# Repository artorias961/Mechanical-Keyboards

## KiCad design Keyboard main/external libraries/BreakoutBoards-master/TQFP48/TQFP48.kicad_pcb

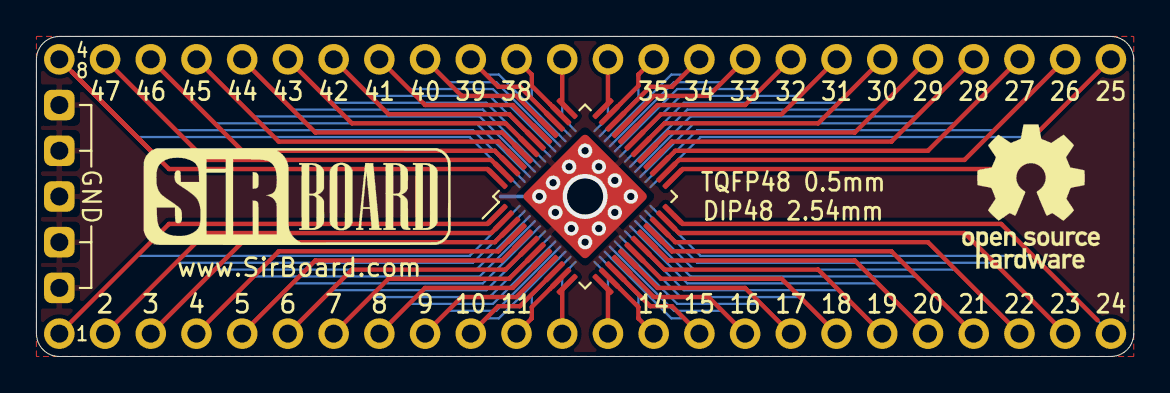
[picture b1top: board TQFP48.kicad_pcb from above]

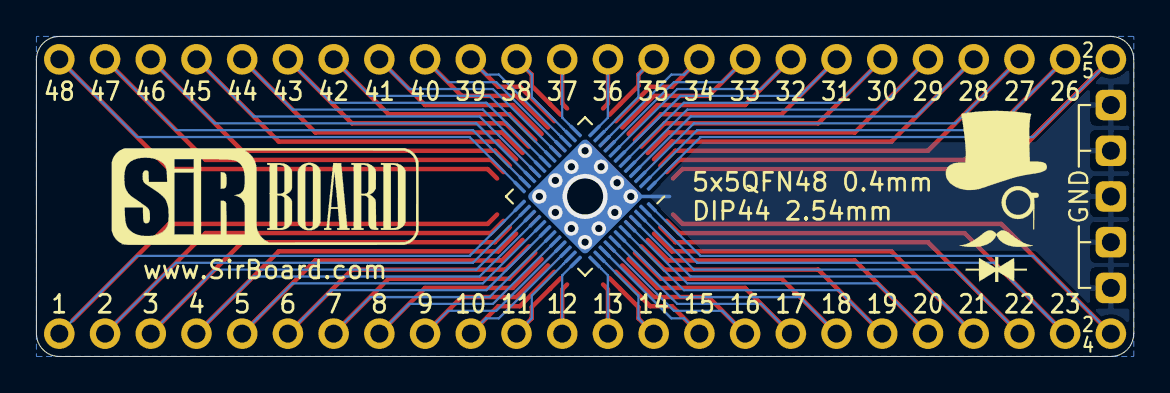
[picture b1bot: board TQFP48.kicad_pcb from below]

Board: 2 copper layers, 61.0 x 17.8 mm, 5 parts (4 on the bottom side), 49 nets.

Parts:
J1, J4: Conn_01x24; PinHeader_1x24_P2.54mm_Vertical
J2: Conn_02x24_Counter_Clockwise; TQFP-48-1EP_7x7mm_P0.5mm_EP5x5mm
J3: Conn_02x24_Counter_Clockwise; UQFN-48-1EP_6x6mm_P0.4mm_EP4.62x4.62mm
J5: Conn_01x05; PinHeader_1x05_P2.54mm_Vertical

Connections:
unnamed: J1.1, J2.1, J3.48
unnamed: J1.2, J2.2, J3.47
unnamed: J1.3, J2.3, J3.46
unnamed: J1.4, J2.4, J3.45
unnamed: J1.5, J2.5, J3.44
unnamed: J1.6, J2.6, J3.43
unnamed: J1.7, J2.7, J3.42
unnamed: J1.8, J2.8, J3.41
unnamed: J1.9, J2.9, J3.40
unnamed: J1.10, J2.10, J3.39
unnamed: J1.11, J2.11, J3.38
unnamed: J1.12, J2.12, J3.37
unnamed: J1.13, J2.13, J3.36
unnamed: J1.14, J2.14, J3.35
unnamed: J1.15, J2.15, J3.34
unnamed: J1.16, J2.16, J3.33
unnamed: J1.17, J2.17, J3.32
unnamed: J1.18, J2.18, J3.31
unnamed: J1.19, J2.19, J3.30
unnamed: J1.20, J2.20, J3.29
unnamed: J1.21, J2.21, J3.28
unnamed: J1.22, J2.22, J3.27
unnamed: J1.23, J2.23, J3.26
unnamed: J1.24, J2.24, J3.25
unnamed: J2.25, J3.24, J4.24
unnamed: J2.26, J3.23, J4.23
unnamed: J2.27, J3.22, J4.22
unnamed: J2.28, J3.21, J4.21
unnamed: J2.29, J3.20, J4.20
unnamed: J2.30, J3.19, J4.19
unnamed: J2.31, J3.18, J4.18
unnamed: J2.32, J3.17, J4.17
unnamed: J2.33, J3.16, J4.16
unnamed: J2.34, J3.15, J4.15
unnamed: J2.35, J3.14, J4.14
unnamed: J2.36, J3.13, J4.13
unnamed: J2.37, J3.12, J4.12
unnamed: J2.38, J3.11, J4.11
unnamed: J2.39, J3.10, J4.10
unnamed: J2.40, J3.9, J4.9
unnamed: J2.41, J3.8, J4.8
unnamed: J2.42, J3.7, J4.7
unnamed: J2.43, J3.6, J4.6
unnamed: J2.44, J3.5, J4.5
unnamed: J2.45, J3.4, J4.4
unnamed: J2.46, J3.3, J4.3
unnamed: J2.47, J3.2, J4.2
unnamed: J2.48, J3.1, J4.1
unnamed: J2.49, J3.49, J5.1, J5.2, J5.3, J5.4, J5.5

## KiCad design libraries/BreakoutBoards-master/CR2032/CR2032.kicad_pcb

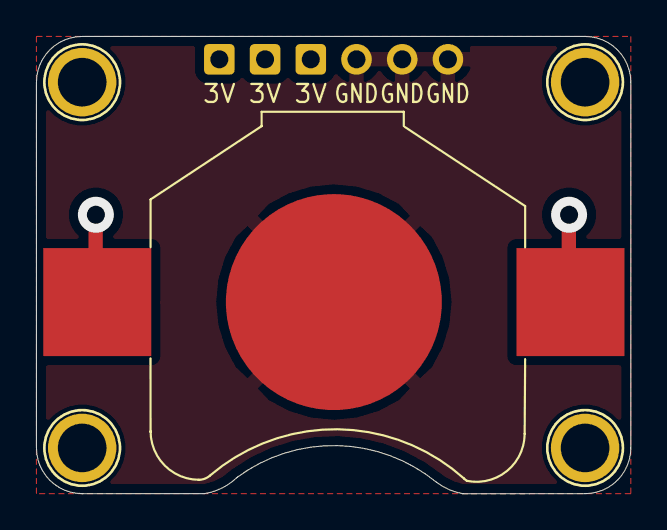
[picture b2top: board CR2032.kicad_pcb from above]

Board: 2 copper layers, 33.0 x 25.4 mm, 6 parts (0 on the bottom side), 2 nets.

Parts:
BT1: Battery_Cell; BatteryHolder_Keystone_3008_1x2450
H1, H2, H3, H4: MountingHole; MountingHole_M2.5_SirBoard
J1: Conn_01x06; PinHeader_1x06_P2.54mm_Vertical

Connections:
+3V0: BT1.1, J1.1, J1.2, J1.3
GND: BT1.2, J1.4, J1.5, J1.6

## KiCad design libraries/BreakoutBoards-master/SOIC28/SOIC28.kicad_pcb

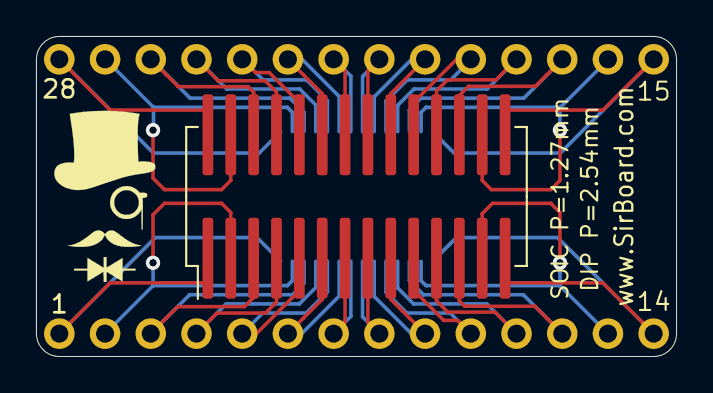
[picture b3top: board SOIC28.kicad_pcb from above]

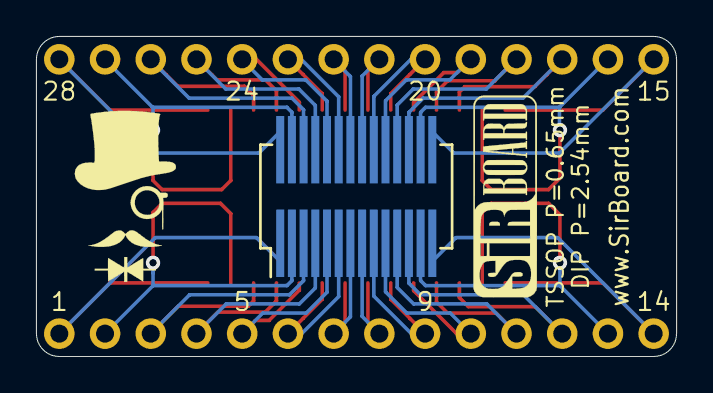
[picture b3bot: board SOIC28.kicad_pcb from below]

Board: 2 copper layers, 35.6 x 17.8 mm, 4 parts (3 on the bottom side), 28 nets.

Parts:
J1, J3: Conn_01x14; PinHeader_1x14_P2.54mm_Vertical
J2: Conn_02x14_Counter_Clockwise; SOIC-28W_7.5x18.7mm_P1.27mm
J4: Conn_02x14_Counter_Clockwise; SSOP-28_5.3x10.2mm_P0.65mm

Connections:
unnamed: J1.1, J2.1, J4.14
unnamed: J1.2, J2.2, J4.13
unnamed: J1.3, J2.3, J4.12
unnamed: J1.4, J2.4, J4.11
unnamed: J1.5, J2.5, J4.10
unnamed: J1.6, J2.6, J4.9
unnamed: J1.7, J2.7, J4.8
unnamed: J1.8, J2.8, J4.7
unnamed: J1.9, J2.9, J4.6
unnamed: J1.10, J2.10, J4.5
unnamed: J1.11, J2.11, J4.4
unnamed: J1.12, J2.12, J4.3
unnamed: J1.13, J2.13, J4.2
unnamed: J1.14, J2.14, J4.1
unnamed: J2.15, J3.14, J4.28
unnamed: J2.16, J3.13, J4.27
unnamed: J2.17, J3.12, J4.26
unnamed: J2.18, J3.11, J4.25
unnamed: J2.19, J3.10, J4.24
unnamed: J2.20, J3.9, J4.23
unnamed: J2.21, J3.8, J4.22
unnamed: J2.22, J3.7, J4.21
unnamed: J2.23, J3.6, J4.20
unnamed: J2.24, J3.5, J4.19
unnamed: J2.25, J3.4, J4.18
unnamed: J2.26, J3.3, J4.17
unnamed: J2.27, J3.2, J4.16
unnamed: J2.8, J3.1, J4.15

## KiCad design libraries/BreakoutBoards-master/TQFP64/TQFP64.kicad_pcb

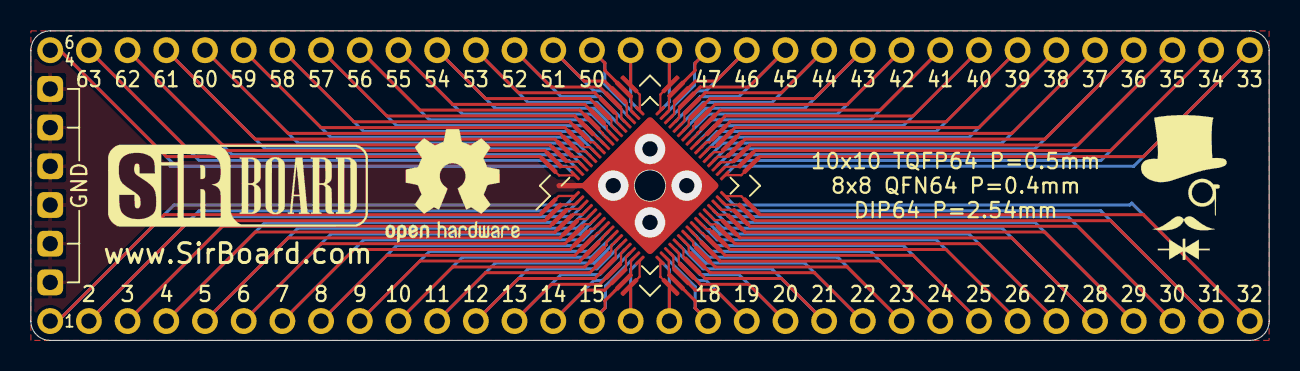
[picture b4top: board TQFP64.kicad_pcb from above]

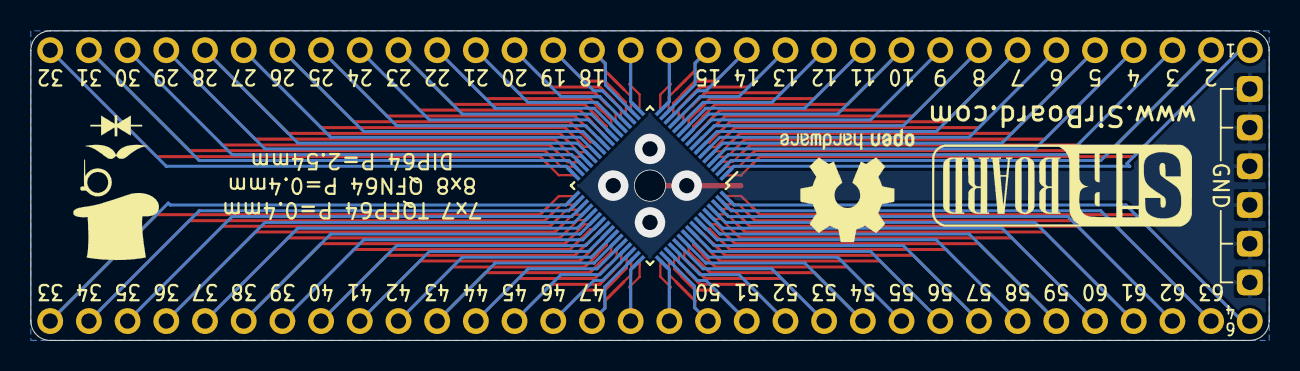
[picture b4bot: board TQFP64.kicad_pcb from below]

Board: 2 copper layers, 81.3 x 20.3 mm, 6 parts (4 on the bottom side), 65 nets.

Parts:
J1, J5: Conn_01x32; PinHeader_1x32_P2.54mm_Vertical
J2: Conn_02x32_Counter_Clockwise; TQFP-64_10x10mm_P0.5mm
J3: Conn_02x32_Counter_Clockwise; QFN-64-1EP_8x8mm_P0.4mm_EP6.5x6.5mm
J4: Conn_02x32_Counter_Clockwise; TQFP-64_7x7mm_P0.4mm
J6: Conn_01x06; PinHeader_1x06_P2.54mm_Vertical

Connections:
unnamed: J1.1, J2.1, J3.1, J4.64
unnamed: J1.2, J2.2, J3.2, J4.63
unnamed: J1.3, J2.3, J3.3, J4.62
unnamed: J1.4, J2.4, J3.4, J4.61
unnamed: J1.5, J2.5, J3.5, J4.60
unnamed: J1.6, J2.6, J3.6, J4.59
unnamed: J1.7, J2.7, J3.7, J4.58
unnamed: J1.8, J2.8, J3.8, J4.57
unnamed: J1.9, J2.9, J3.9, J4.56
unnamed: J1.10, J2.10, J3.10, J4.55
unnamed: J1.11, J2.11, J3.11, J4.54
unnamed: J1.12, J2.12, J3.12, J4.53
unnamed: J1.13, J2.13, J3.13, J4.52
unnamed: J1.14, J2.14, J3.14, J4.51
unnamed: J1.15, J2.15, J3.15, J4.50
unnamed: J1.16, J2.16, J3.16, J4.49
unnamed: J1.17, J2.17, J3.17, J4.48
unnamed: J1.18, J2.18, J3.18, J4.47
unnamed: J1.19, J2.19, J3.19, J4.46
unnamed: J1.20, J2.20, J3.20, J4.45
unnamed: J1.21, J2.21, J3.21, J4.44
unnamed: J1.22, J2.22, J3.22, J4.43
unnamed: J1.23, J2.23, J3.23, J4.42
unnamed: J1.24, J2.24, J3.24, J4.41
unnamed: J1.25, J2.25, J3.25, J4.40
unnamed: J1.26, J2.26, J3.26, J4.39
unnamed: J1.27, J2.27, J3.27, J4.38
unnamed: J1.28, J2.28, J3.28, J4.37
unnamed: J1.29, J2.29, J3.29, J4.36
unnamed: J1.30, J2.30, J3.30, J4.35
unnamed: J1.31, J2.31, J3.31, J4.34
unnamed: J1.32, J2.32, J3.32, J4.33
unnamed: J2.33, J3.33, J4.32, J5.32
unnamed: J2.34, J3.34, J4.31, J5.31
unnamed: J2.35, J3.35, J4.30, J5.30
unnamed: J2.36, J3.36, J4.29, J5.29
unnamed: J2.37, J3.37, J4.28, J5.28
unnamed: J2.38, J3.38, J4.27, J5.27
unnamed: J2.39, J3.39, J4.26, J5.26
unnamed: J2.40, J3.40, J4.25, J5.25
unnamed: J2.41, J3.41, J4.24, J5.24
unnamed: J2.42, J3.42, J4.23, J5.23
unnamed: J2.43, J3.43, J4.22, J5.22
unnamed: J2.44, J3.44, J4.21, J5.21
unnamed: J2.45, J3.45, J4.20, J5.20
unnamed: J2.46, J3.46, J4.19, J5.19
unnamed: J2.47, J3.47, J4.18, J5.18
unnamed: J2.48, J3.48, J4.17, J5.17
unnamed: J2.49, J3.49, J4.16, J5.16
unnamed: J2.50, J3.50, J4.15, J5.15
unnamed: J2.51, J3.51, J4.14, J5.14
unnamed: J2.52, J3.52, J4.13, J5.13
unnamed: J2.53, J3.53, J4.12, J5.12
unnamed: J2.54, J3.54, J4.11, J5.11
unnamed: J2.55, J3.55, J4.10, J5.10
unnamed: J2.56, J3.56, J4.9, J5.9
unnamed: J2.57, J3.57, J4.8, J5.8
unnamed: J2.58, J3.58, J4.7, J5.7
unnamed: J2.59, J3.59, J4.6, J5.6
unnamed: J2.60, J3.60, J4.5, J5.5
unnamed: J2.61, J3.61, J4.4, J5.4
unnamed: J2.62, J3.62, J4.3, J5.3
unnamed: J2.63, J3.63, J4.2, J5.2
unnamed: J2.64, J3.64, J4.1, J5.1
unnamed: J3.65, J6.1, J6.2, J6.3, J6.4, J6.5, J6.6
